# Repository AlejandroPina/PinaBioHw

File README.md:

[English](#) | [Español](README.es.md)

**Versión en español:** [README.es.md](README.es.md)

# PinaBio v1.0 (Paca)

The **paid JLCPCB order** is **v1.0** (`exports/PinaBio_v1_*`). A **v1.1 layout** (XIAO USB at the board edge) is ready for a **later** spin: `exports/PinaBio_v1.1_*` and `docs/10_pinabio_v1.1_rf.md`. Same circuit. Do not mix v1.1 files into the current order.

**PinaBio** is a **biofeedback** board (skin conductance, pulse, temperature, ECG, breathing). It is **not a medical device** and does not diagnose anything. The nickname **Paca** is a tribute to Alejandro’s grandmother.

Phone Bluetooth advertises as **`PinaBiosensor`**. Keep this BLE name for firmware clients.

## What the board is

One PCB, about **110 × 70 mm**, microcontroller **Seeed XIAO ESP32-S3** in a socket:

- GSR (skin)
- Pulse / HRV (MAX30102) — raw PPG for external HRV analysis
- Temperature (MAX30205)
- ECG (AD8232 module — lab toy, not a hospital ECG)
- Chest + abdomen breathing (stretch bands that change resistance)

Older notes call this same board “Completa”. KiCad files stay named `PinaBiosensor_Mini.*` on purpose (renaming breaks the project). Silk says **PINA** / **PINABio v1.0** (no “Paca” on copper — it does not fit).

Charge the XIAO from its USB-C. **With electrodes or bands on skin: Bluetooth only. Never USB from a PC and skin at the same time.**

The paid v1.0 fabrication trio is in `exports/` on `main`: `PinaBio_v1_gerbers.zip`, `PinaBio_v1_bom_jlc.csv` and `PinaBio_v1_cpl.csv`. Their committed bytes match `exports/archive_v1.0/SHA256SUMS`. See the [order guide](docs/08_jlcpcb_order.md) before a repeat order.

## Safety (read this)

This design is **not** USB-isolated. Full text: `docs/04_seguridad.md`.

1. **Never** USB to a computer while GSR, bands, or ECG electrodes are on the body.
2. Charge / flash firmware with **skin disconnected**.
3. A session with skin = **BLE only**.
4. LiPo **with a protection board** only. JST J1: pin 1 +, pin 2 ground.
5. Not for diagnosis, not for use on wounds, not a medical product.

## Order PCBs (JLCPCB)

**5** bare boards, **2** assembled (PCBA). Step-by-step: [English order guide](docs/08_jlcpcb_order.md) · [Español](docs/08_pedido_jlcpcb.md).

For a repeat order, use the three `PinaBio_v1_*` files in `exports/` on `main` and verify their hashes against `exports/archive_v1.0/SHA256SUMS`. The old `kicad-completa` branch is no longer needed. Do **not** substitute the loose `exports/gerbers/` files or the v1.1 package.

## Firmware

Board sketch (Arduino, XIAO ESP32-S3):

`firmware/PinaBiosensor_Firmware_v1_3/PinaBiosensor_Firmware_v1_3.ino`

Firmware 1.2 is kept at `firmware/PinaBiosensor_Firmware_v1_2/` for rollback.

BLE name: `PinaBiosensor`. Current protocol: `docs/firmware_v1_3_protocol.en.md` (binary byte still `0x12`, same as 1.2). Instructions: `firmware/README.md`. Changes: `firmware/CHANGELOG_v1_3.md`.

Firmware debug JSON is v4. Binary frame details are in the protocol specification.

## Open the PCB in KiCad

See `docs/03_guia_kicad.md`. Short version:

1. Install [KiCad 8](https://www.kicad.org/) **with libraries**. Do not create a new project.
2. Open `hardware/PinaBiosensor_Mini.kicad_pro`.
3. The schematic is a text map. The board you order is the PCB.

## Suggested fab (summary)

- JLCPCB / PCBWay, 2 layers, FR4 1.6 mm, green mask, HASL or ENIG.
- Factory SMT: 1206, SOT-23-5, SOIC-14, ADS1115 (VSSOP-10, very small).
- You fit: XIAO, MAX/AD8232 modules, battery, box switch on **J9**, optional meter on **J10**.

Design BOM: `bom/BOM.csv`.

## More docs

- `docs/02_arquitectura.md` — architecture
- `docs/04_seguridad.md` — safety (EN + ES)
- `docs/firmware_v1_3_protocol.en.md` — BLE UUIDs and current frames (byte `0x12`)
- `docs/firmware_v1_2_protocol.en.md` — V1.2 frames (kept for rollback)
- `docs/08_jlcpcb_order.md` — order (English)
- `docs/08_pedido_jlcpcb.md` — pedido (español)
- `docs/09_caja_interruptor_medidor.md` — box DPDT (4 wires) and J10

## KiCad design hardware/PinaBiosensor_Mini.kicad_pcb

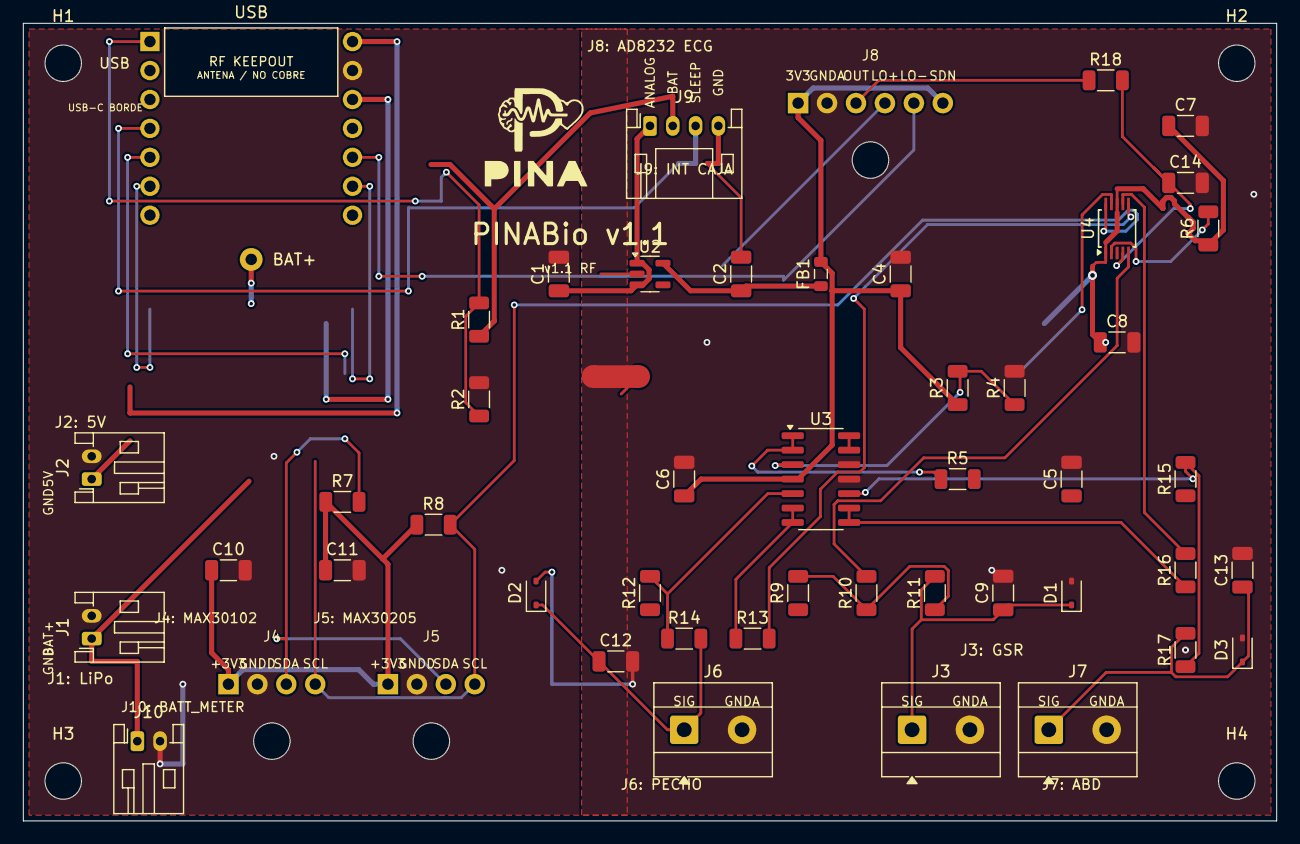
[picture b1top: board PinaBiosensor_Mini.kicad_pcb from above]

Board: 2 copper layers, 110.0 x 70.0 mm, 55 parts (0 on the bottom side), 31 nets.

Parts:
C1, C2, C8: 1uF; C_1206_3216Metric
C4: 10uF; C_1206_3216Metric
C5: 4.7uF; C_1206_3216Metric
C6, C7, C9, C10, C11, C12, C13, C14: 100nF; C_1206_3216Metric
D1, D2, D3: PESD5V0S1UL; D_SOD-323
FB1: 600R@100MHz; L_0805_2012Metric
H1, H2, H3, H4: M3; MountingHole_3.2mm_M3
J1: LiPo_JST-PH; JST_PH_S2B-PH-K_1x02_P2.00mm_Horizontal
J2: 5V_CHARGE; JST_PH_S2B-PH-K_1x02_P2.00mm_Horizontal
J3: GSR; TerminalBlock_MetzConnect_Type101_RT01602HBWC_1x02_P5.08mm_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
J4: MAX30102; SensorCable_4P_Anchor
J5: MAX30205; SensorCable_4P_Anchor
J6: RESP_THORAX; TerminalBlock_MetzConnect_Type101_RT01602HBWC_1x02_P5.08mm_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
J7: RESP_ABDOMEN; TerminalBlock_MetzConnect_Type101_RT01602HBWC_1x02_P5.08mm_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
J8: AD8232; SensorCable_6P_Anchor
J9: INT_CAJA_DPDT; JST_PH_S4B-PH-K_1x04_P2.00mm_Horizontal
J10: BATT_METER; JST_PH_S2B-PH-K_1x02_P2.00mm_Horizontal
LOGO: PINA_Logo
NT1: NetTie_2; NetTie-2_SMD_Pad2.0mm
R1, R2, R12, R15: 47k 1%; R_1206_3216Metric
R3: 56k 0.1%; R_1206_3216Metric
R4: 10k 0.1%; R_1206_3216Metric
R5: 47; R_1206_3216Metric
R6: 10k; R_1206_3216Metric
R7, R8: 2.2k; R_1206_3216Metric
R9: 100k; R_1206_3216Metric
R10, R13, R16: 470; R_1206_3216Metric
R11, R14, R17, R18: 1k; R_1206_3216Metric
U1: XIAO_ESP32S3; XIAO_ESP32S3_Socket
U2: ADP150AUJZ-3.3; SOT-23-5
U3: MCP6004; SOIC-14_3.9x8.7mm_P1.27mm
U4: ADS1115IDGS; TSSOP-10_3x3mm_P0.5mm

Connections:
+3V3: C7.1, C8.1, C10.1, C11.1, J4.1, J5.1, R6.1, R7.1, R8.1, U1.12, U4.1, U4.8
+5V: J2.1, U1.14
AB_AIN: R16.2, U4.7
AB_ELEC: C13.1, D3.1, J7.1, R17.2
AB_MID: R15.2, R17.1, U3.10
ADS_ALERT: R6.2, U4.2
ECG_AIN: C14.1, R18.2, U4.4
ECG_LON: J8.5, U1.10
ECG_LOP: J8.4, U1.9
ECG_OUT: J8.3, R18.1
GNDA: C4.2, C5.2, C6.2, C7.2, C8.2, C9.2, C12.2, C13.2, C14.2, D1.2, D2.2, D3.2, J3.2, J6.2, J7.2, J8.2, NT1.1, R4.2, U3.11, U3.12, U4.3
GNDD: C1.2, C2.2, C10.2, C11.2, J1.2, J2.2, J4.2, J5.2, J9.4, J10.2, NT1.2, R2.2, U1.13, U2.2
GSR_AIN: R10.2, U4.5
GSR_ELEC: C9.1, D1.1, J3.1, R11.2
GSR_MID: R9.2, R10.1, R11.1
LDO_OUT: C2.1, FB1.1, U2.5
LDO_VIN: C1.1, J9.1, U2.1, U2.3
unnamed: R5.1, U3.1, U3.2
unnamed: R13.1, U3.6, U3.7
unnamed: R16.1, U3.8, U3.9
unnamed: U3.13, U3.14
SCL: J4.4, J5.4, R8.2, U1.6, U4.10
SDA: J4.3, J5.3, R7.2, U1.5, U4.9
SLEEP_N: J9.3, U1.4
TH_AIN: R13.2, U4.6
TH_ELEC: C12.1, D2.1, J6.1, R14.2
TH_MID: R12.2, R14.1, U3.5
VBAT_DIV: R1.2, R2.1, U1.1
VREF_DIV: R3.2, R4.1, U3.3
V_ANALOG: C4.1, C6.1, FB1.2, J8.1, J8.6, R3.1, U3.4
V_BATT: J1.1, J9.2, J10.1, R1.1, U1.15

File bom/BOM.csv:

PinaBio v1.0,Ref,Value,Footprint,Qty,LCSC,Notas
Seeed XIAO ESP32-S3 (modulo),U1,XIAO_ESP32S3,Pina:XIAO_ESP32S3_Socket,1,,DNP modulo; zocalo 2x hembra 1x7 2.54mm + pad BAT+; emparejar en web (p.ej. C2932672 x2) o suelda Alejandro
ADP150AUJZ-3.3,U2,3.3V LDO,SOT-23-5,1,C29149,ADP150AUJZ-3.3-R7 TSOT-23-5; JLC Extended
MCP6004-I/SL,U3,MCP6004,SOIC-14,1,C1346056,SOIC-14; JLC Extended
ADS1115IDGSR,U4,ADS1115,VSSOP-10,1,C37593,ADS1115IDGSR VSSOP-10; JLC Extended
Ferrita 600ohm,FB1,600R@100MHz,0805,1,C113034,BLM21AJ601SN1D 600ohm@100MHz 0805 Murata
R 47k 1%,R1 R2 R12 R15,47k,1206,4,C25833,1206W4F4702T5E UNI-ROYAL 1%; JLC Extended (no hay Basic 1206 47k)
R 56k 0.1%,R3,56k,1206,1,C4257433,MCA12060D5602BP100 Vishay 0.1%; Extended; stock en web
R 10k 0.1%,R4,10k,1206,1,C2507497,RNCF1206BTC10K0 Stackpole 0.1%; Extended; stock en web
R 47 1%,R5,47,1206,1,C17969,1206W4F470JT5E UNI-ROYAL; Extended
R 10k 1%,R6,10k,1206,1,C17902,1206W4F1002T5E UNI-ROYAL; JLC Basic
R 2.2k 1%,R7 R8,2.2k,1206,2,C17948,1206W4F2201T5E UNI-ROYAL; Extended
R 100k 1%,R9,100k,1206,1,C17900,1206W4F1003T5E UNI-ROYAL; JLC Basic
R 470 1%,R10 R13 R16,470,1206,3,C4502,1206W4F4700T5E UNI-ROYAL; Extended
R 1k 1%,R11 R14 R17 R18,1k,1206,4,C4410,1206W4F1001T5E UNI-ROYAL; JLC Basic
C 1uF,C1 C2 C8,1uF,1206,3,C1848,CL31B105KBHNNNE 1uF 50V X7R 1206 Samsung; JLC Basic
C 10uF,C4,10uF,1206,1,C13585,CL31A106KBHNNNE 10uF 50V X5R 1206 Samsung; JLC Basic
C 4.7uF,C5,4.7uF,1206,1,C29823,1206B475K500NT 4.7uF 50V X7R 1206 FH; JLC Basic
C 100nF,C6 C7 C9 C10 C11 C12 C13 C14,100nF,1206,8,C24497,CL31B104KBCNNNC 100nF 50V X7R 1206 Samsung; JLC Basic
TVS 5V SOD-323,D1 D2 D3,PESD5V0S1BA,SOD-323,3,C19224,PESD5V0S1BA SOD-323 bidir (PESD5V0S1UL es DFN1006; no encaja en este footprint)
Net-tie,NT1,NetTie-2,,1,,DNP / cobre; no es componente de fabrica
JST PH 2P,J1 J2 J10,LiPo / 5V / BATT METER,JST_PH_S2B-PH-K,3,C173752,S2B-PH-K-S(LF)(SN) TH R/A; JLC wave/THT
JST PH 4P,J9,INT CAJA DPDT,JST_PH_S4B-PH-K,1,C157926,S4B-PH-K-S(LF)(SN) TH R/A; fabrica monta conector NO slide
Borne 2P 5.08,J3 J6 J7,GSR / pecho / abdomen,Metz RT01602HBWC 5.08 2P H,3,,emparejar en web: Metz RT01602HBWC; candidato KF128R-5.08-2P C475082 (verificar cuerpo vs footprint)
Pads 4P,J4 J5,MAX30102 / MAX30205,Pina:SensorCable_4P_Anchor,2,,DNP fabrica (solo pads)
Pads 6P,J8,AD8232,Pina:SensorCable_6P_Anchor,1,,DNP fabrica (solo pads)
M3,H1-H4,M3,MountingHole_3.2mm_M3,4,,DNP
SW1 (no existe),,,,0,,No hay slide en placa; DPDT va en panel/caja a J9
Modulo MAX30102,,,,1,,DNP fabrica
Modulo MAX30205,,,,1,,DNP fabrica
Modulo AD8232,,,,1,,DNP fabrica
Banda goma resistiva pecho,,,,1,,
Banda goma resistiva abdomen,,,,1,,
LiPo 1S con proteccion,,,,1,,
Electrodos GSR,,,,1,,
Electrodos ECG del AD8232,,,,1,,
NOTA ensamblaje,,,,,,"Soldar todo SMD (ADS1115, resto), zocalo XIAO, J1 J2 J10, bornes J3 J6 J7, conector J9. NO montar slide SW1. LCSC verificados en jlcpcb.com/lcsc.com 2026-09-12; stock y Basic/Extended cambian — revisar en el carrito."
